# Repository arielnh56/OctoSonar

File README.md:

# OctoSonar library for Arduino
Version: 1.2.0<br>
Release date: 1/14/2018<br>
https://hackaday.io/project/19950-hc-sr04-i2c-octopus-octosonar
https://redhunterstore.etsy.com/listing/1151819630/octosonar-connect-8-x-hc-sr04-to-arduino

## Summary

This is a library for the Arduino IDE that allows the polling of multiple ultrasonic distance sensors using the I2C 
bus and a single hardware interrupt pin. It assumes a PCF8574(A) or PCF8575 type port expander to trigger the sensors, and 
tri-state buffers to multiplex the echo signals. It is specifically developed and maintained to support the author's 
OctoSonar boards version 2.0+ and OctoSonarX2. For earlier boards see the SonarI2C library.

It has been developed for use with the HC-SR04 sensor - and has been tested with units from multiple manufacturers.

## Supported Platforms

This library is designed to work with the Arduino IDE versions 1.6.x or later; it is not tested it with earlier versions. It should work with any Arduino compatible board with an available hardware interrupt pin. Note that other interrupt 
activity may interfere with the accuracy and reliability of this code.

## Getting Started

### Hardware

This code supports the OctoSonar v2.0 and later and OctoSonarX2. Schematics and board designs are included in this repo.

Boards and sensors can be purchased at [on Etsy.](https://redhunterstore.etsy.com)

The board should be connected to your controller as follows:

* GND -> GND
* VCC -> VCC (5V on the UNO)
* SDA -> SDA (A4 in the UNO)
* SCL -> SCL (A5 on the UNO)
* INT -> a hardware interrupt pin (2 or 3 on the UNO)
* 5V -> a 5V supply (VCC on the UNO)

Note that the 5V supply drives the sensors and the VCC drives the electronics. This allows the unit to be supported
on 3.3V controllers (some Arduino formats and Raspberry Pi, Teensy etc). You can save a wire on a 5V controller
by connecting the 5V and VCC pins together via the V1 solder jumper.

As manufactured the board has an I2C address of 0x38. This can be altered via solder jumpers on the back.

The I2C bus **requires** pullup resistors on the SDA and SCL lines to VCC. While Arduinos will enable the
internal pullups, these are too large at 20k - 50k for reliable operation of I2C. The generally recommended 
value to use is 4.7k. Positions are provided on the board at R1 and R2 to add these pullup resistors. On my 
projects I usually have several devices on the bus and place the pullups near the controller. For more information on
use of the I2C bus there is an [excellent Sparkfun tutorial.](https://learn.sparkfun.com/tutorials/i2c)

### Software

If you are using version 1.6.2 or later of the [Arduino software (IDE)](http://www.arduino.cc/en/Main/Software), you 
can use the Library Manager to install this library:

1. In the Arduino IDE, open the "Sketch" menu, select "Include Library", then "Manage Libraries...".
2. Search for "OctoSonar".
3. Click the OctoSonar entry in the list.
4. Click "Install".

If this does not work, you can manually install the library:

1. Download the [latest release archive from GitHub](https://github.com/arielnh56/OctoSonar/releases) and decompress it.
2. Rename the folder "OctoSonar-master" to "OctoSonar".
3. Move the "OctoSonar" folder into the "libraries" directory inside your Arduino sketchbook directory.  You can view your sketchbook location by opening the "File" menu and selecting "Preferences" in the Arduino IDE.  If there is not already a "libraries" folder in that location, you should make the folder yourself.
4. After installing the library, restart the Arduino IDE.

(note - the above instructions adapted from a Pololu readme)

## Examples

Examples are included to show basic functionality and use:

* OctoSonarTest - exercises the OctoSonar board and sends serial output at 115200 baud
* OctoSonarTestLCD - exercises the OctoSonar board and display output to LCD
* OctoSonarX2Test - exercises the OctoSonarX2 board and sends serial output at 115200 baud
* OctoSonarX2Test12LCD - exercises the OctoSonarX2 board and displays output on a two LCDs. Assumes 12 sensors mounted on my trimount brackets, with the diagonal sensor output displayed on the secondary LCD

The "bench" examples drive the test jigs used during quality control. Do no use these examples, they will not work for you.

## Library reference

* Constructor. Call once outside loop() and setup(). This sets the I2C address of the pin expander (0x38 - 0x3F for OctoSonar, 0x20 - 0x27 for OctoSonarX2).
e.g.  OctoSonar() myOcto;

 ```c
    OctoSonar(); // defaults constructor 0x38, 2
    OctoSonar(uint8_t address, uint8_t interrupt); // constructor
    OctoSonarX2(); // defaults constructor 0x20, 2
    OctoSonarX2(uint8_t address, uint8_t interrupt); // constructor
 
```

* call one of the begin() functions from setup(). The second one of these lets you set the active ports up front.
e.g. myOcto.begin();

 ```c
    void begin();
    void begin(uint16_t active);
```

*  Disabling sensors that you are not interested in right now allows the other sensors to poll more often. This is a bitmask mapping to the 16 sensors on the unit. A '1' is 'active'. 
e.g. myOcto.active = 0x0003;   // S0 and S1 only

 ```c
    uint16_t active;                    // mask of active sensors 
```

* by default we skip one out of range/failed echo, keeping the last value. It may be useful to raise this count in sub-optimal echo environments. This is a global setting.
e.g. OctoSonar::maxOOR = 2;

 ```c
    static uint8_t maxOOR;                                   // how many OOR to skip. Raise this in noisy environments
```

* by default the output is in mm. You can change this by setting this to OCTOSONAR_CM for cm, or OCTOSONAR_IN for inches. It is the value needed to convert from microseconds to the desired unit. This is a global setting.
e.g. OctoSonar::units = OCTOSONAR_IN;

 ```c
    static double units;                        // defaults to OCTOSONAR_MM 
```

* Call this every loop(). If it is time, it will poll the next enabled sensor. 
e.g. OctoSonar::doSonar();

 ```c
    static void doSonar();
```

* Return values. By default, when the sensor does not get a good echo a zero value is returned. Using the second
  form of read() allows you to set your own preference for what is returned. The returned value defaults to mm.
e.g. int16_t distance = myOcto.read(1);  // read distance from S1
 ```c
    int16_t read(uint8_t sonar);                     
    int16_t read(uint8_t sonar, int16_t outOfRange);
```

## Using multiple boards
The code is written to support multiple OctoSonar units on the same or different interrupt pins. It will cycle
through all the active sensors on one board, then move on to the next board, in a loop. It will not poll 
multiple boards in
parallel. At the time of writing (6/30/2017) I haven't actually tested this multi-board capability. It uses 
similar logic to that used in the earlier SonarI2C library, except that it is the boards that are in a 
looped-linked-list not the sensors.
 
## Relationship to SonarI2C

This is a rework of the SonarI2C concept, and borrows a lot from it. It is structurally different so I'm
 starting a new repo.

The main differences are:
* the use of tri-state buffers to mux the echo signals
* the trigger pulse is held down for the duration of each sensor. The falling edge triggers the HC-SR04, and the low value is used to enable the 
matching tri-state buffer to forward the echo signal
* the unit of thing is now the board, not the sensor. 
* No daisy-chaining. That was silly.

## Version history
* 1.2.0 (1/14/2018): Updated eagle files. Updated examples. No changes to library code.
* 1.1.0 (7/26/2017): OctoSonarX2 support working - moved to derived classes
* 1.0.1 (7/1/2017): Included correct OctoSonarTest example
* 1.0.0 (06/30/2017): Initial release

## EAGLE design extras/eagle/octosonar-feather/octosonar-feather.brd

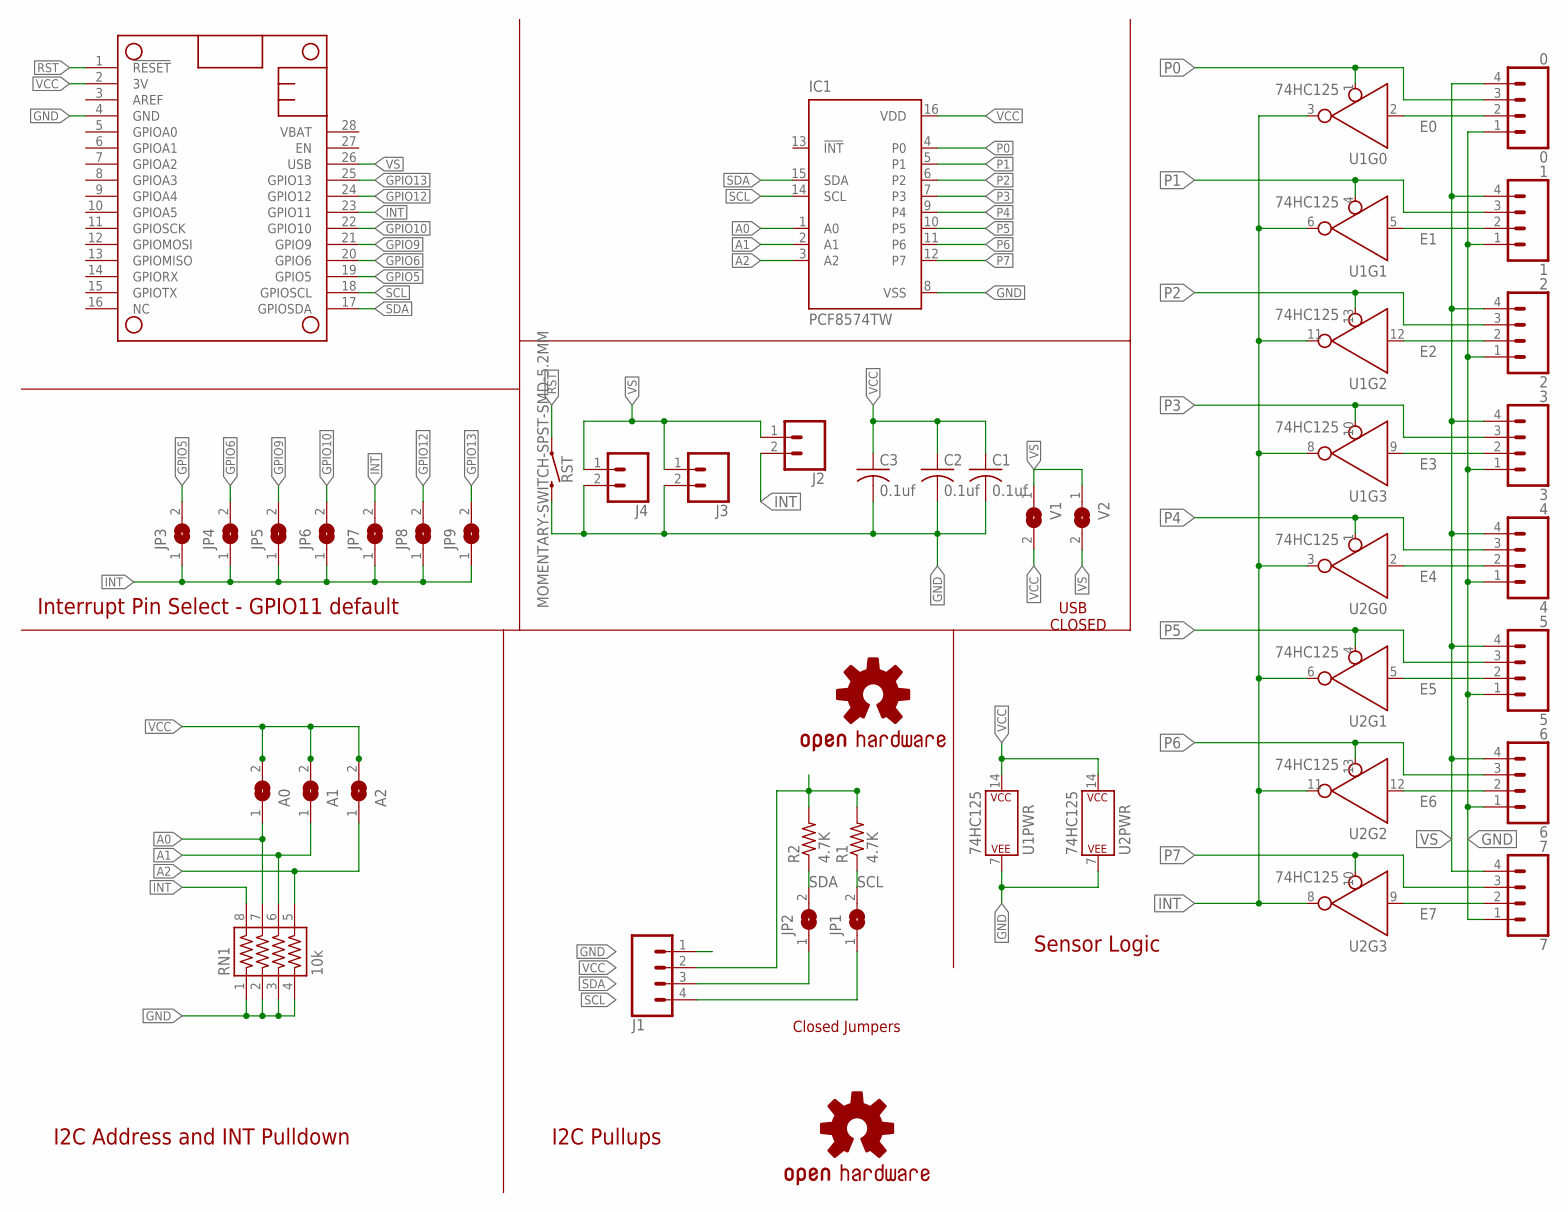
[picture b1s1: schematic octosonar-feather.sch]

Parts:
0: 0; 1X04_NO_SILK
1: 1; 1X04_NO_SILK
2: 2; 1X04_NO_SILK
3: 3; 1X04_NO_SILK
4: 4; 1X04_NO_SILK
5: 5; 1X04_NO_SILK
6: 6; 1X04_NO_SILK
7: 7; 1X04_NO_SILK
A0, A1, A2: SJSJ-NOCREAM; SJ-NOCREAM
C1, C2, C3: 0.1uf; C0603
IC1: PCF8574TW; SO16W
J1: CONN_041X04_NO_SILK; 1X04_NO_SILK
J2, J3, J4: CONN_021X02_NO_SILK; 1X02_NO_SILK
JP1, JP2, JP3, JP4, JP5, JP6, JP7, JP8, JP9: SJSJ-NOCREAM; SJ-NOCREAM
LOGO1: OSHW-LOGOL-COPPER; OSHW-LOGO-L_COPPER
LOGO2: OSHW-LOGOL; OSHW-LOGO-L
MS1: FEATHERWINGFEATHERWING_LONG; FEATHERWING_LONG
R1, R2: 4.7K; R0603
RN1: 10k; 743-8
RST: MOMENTARY-SWITCH-SPST-SMD-5.2MM; TACTILE_SWITCH_SMD_5.2MM
U1, U2: 74HC125; SO14
V1, V2: SJSJ-NOCREAM; SJ-NOCREAM

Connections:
A0: A0.1, IC1.1 (A0), RN1.7
A1: A1.1, IC1.2 (A1), RN1.6
A2: A2.1, IC1.3 (A2), RN1.5
E0: 0.2, U1.2 (A)
E1: 1.2, U1.5 (A)
E2: 2.2, U1.12 (A)
E3: 3.2, U1.9 (A)
E4: 4.2, U2.2 (A)
E5: 5.2, U2.5 (A)
E6: 6.2, U2.12 (A)
E7: 7.2, U2.9 (A)
GND: 0.1, 1.1, 2.1, 3.1, 4.1, 5.1, 6.1, 7.1, C1.2, C2.2, C3.2, IC1.8 (VSS), J1.1, J3.2, J4.2, MS1.4 (GND), RN1.1, RN1.2, RN1.3, RN1.4, RST.3 (2), U1.7 (P$V-), U2.7 (P$V-)
GPIO5: JP3.2, MS1.19 (GPIO5)
GPIO6: JP4.2, MS1.20 (GPIO6)
GPIO9: JP5.2, MS1.21 (GPIO9)
GPIO10: JP6.2, MS1.22 (GPIO10)
GPIO12: JP8.2, MS1.24 (GPIO12)
GPIO13: JP9.2, MS1.25 (GPIO13)
INT: J2.2, JP3.1, JP4.1, JP5.1, JP6.1, JP7.1, JP7.2, JP8.1, JP9.1, MS1.23 (GPIO11), RN1.8, U1.3 (Y), U1.6 (Y), U1.8 (Y), U1.11 (Y), U2.3 (Y), U2.6 (Y), U2.8 (Y), U2.11 (Y)
P0: 0.3, IC1.4 (P0), U1.1 (!EN)
P1: 1.3, IC1.5 (P1), U1.4 (!EN)
P2: 2.3, IC1.6 (P2), U1.13 (!EN)
P3: 3.3, IC1.7 (P3), U1.10 (!EN)
P4: 4.3, IC1.9 (P4), U2.1 (!EN)
P5: 5.3, IC1.10 (P5), U2.4 (!EN)
P6: 6.3, IC1.11 (P6), U2.13 (!EN)
P7: 7.3, IC1.12 (P7), U2.10 (!EN)
RST: MS1.1 (!RESET), RST.1
SCL: IC1.14 (SCL), J1.4, JP1.1, JP1.2, MS1.18 (GPIOSCL), R1.1
SDA: IC1.15 (SDA), J1.3, JP2.1, JP2.2, MS1.17 (GPIOSDA), R2.1
VCC: A0.2, A1.2, A2.2, C1.1, C2.1, C3.1, IC1.16 (VDD), J1.2, MS1.2 (3V), R1.2, R2.2, U1.14 (P$V+), U2.14 (P$V+), V1.2
VS: 0.4, 1.4, 2.4, 3.4, 4.4, 5.4, 6.4, 7.4, J2.1, J3.1, J4.1, MS1.26 (USB), V1.1, V2.1, V2.2

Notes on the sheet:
Sensor Logic
I2C Pullups
I2C Address and INT Pulldown
Interrupt Pin Select - GPIO11 default
USB CLOSED
Closed Jumpers

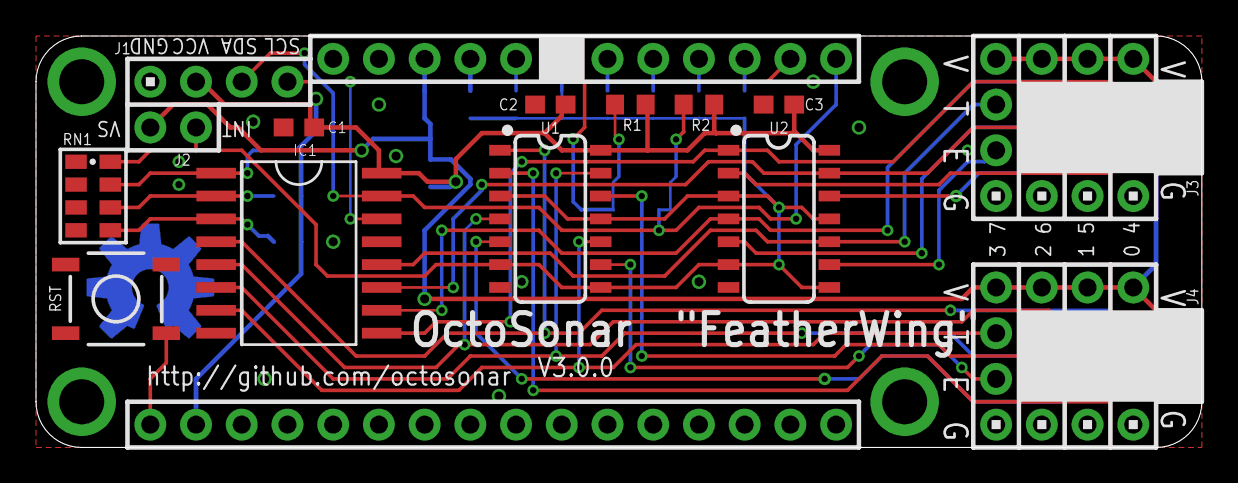
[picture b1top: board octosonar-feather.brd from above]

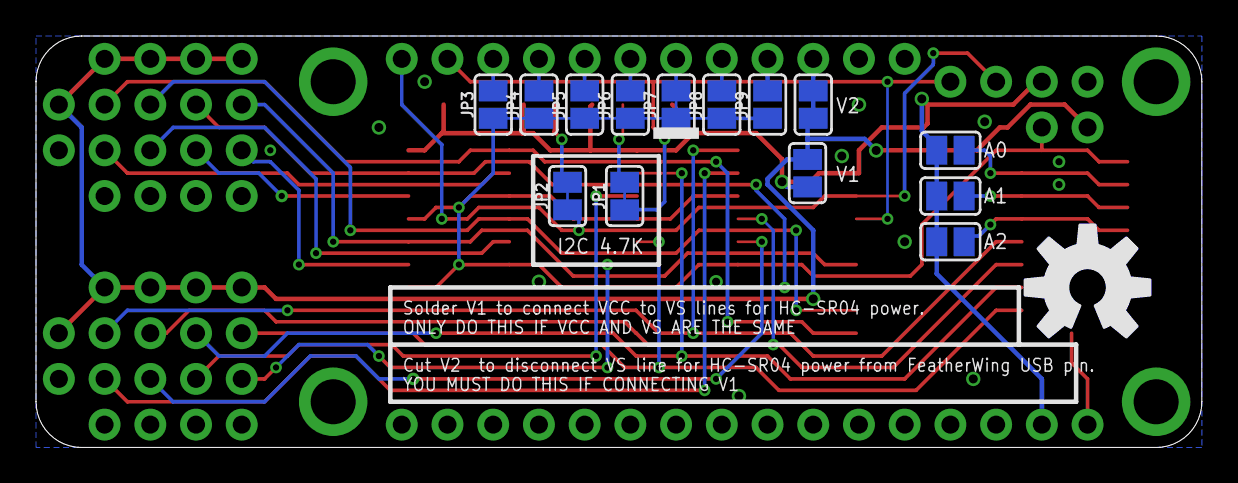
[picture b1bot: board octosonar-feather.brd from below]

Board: 2 copper layers, 64.8 x 22.9 mm, 39 parts (16 on the bottom side), 32 nets.

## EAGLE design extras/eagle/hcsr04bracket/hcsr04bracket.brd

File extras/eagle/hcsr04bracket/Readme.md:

This is the 1.0.0 initial batch. The diagonal sensor is 0.1" too far back, so
the pins on that sensor need re-bending.

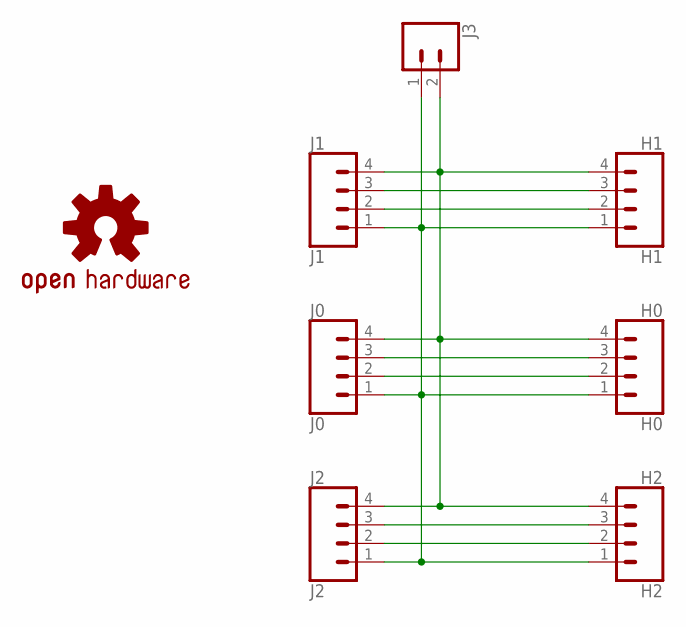
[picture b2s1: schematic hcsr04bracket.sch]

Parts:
H0: H0; 1X04
H1: H1; 1X04
H2: H2; 1X04
J0: J0; 1X04
J1: J1; 1X04
J2: J2; 1X04
J3: CONN_02; 1X02
LOGO1: OSHW-LOGOS; OSHW-LOGO-S

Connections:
E1: H1.3, J1.3
E2: H0.3, J0.3
E3: H2.3, J2.3
GND: H0.4, H1.4, H2.4, J0.4, J1.4, J2.4, J3.2
T1: H1.2, J1.2
T2: H0.2, J0.2
T3: H2.2, J2.2
VCC: H0.1, H1.1, H2.1, J0.1, J1.1, J2.1, J3.1

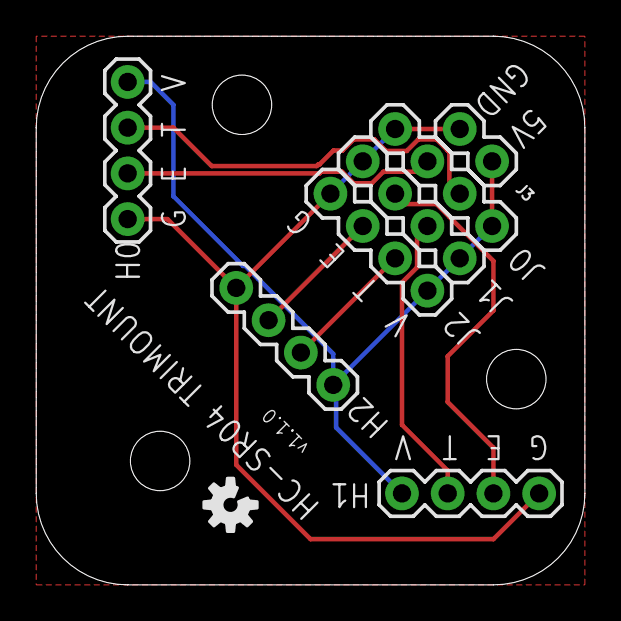
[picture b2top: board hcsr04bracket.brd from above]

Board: 2 copper layers, 30.5 x 30.5 mm, 11 parts (1 on the bottom side), 8 nets.

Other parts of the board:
U$1, U$2, U$3: STAND-OFF

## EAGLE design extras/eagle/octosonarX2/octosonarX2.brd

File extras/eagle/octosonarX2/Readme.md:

This is 1.0.0 batch.

It differs from the 0.0.1 prototype with changes in bypass caps and a re-routing
of the power around the board with a wider track. This now runs closer than
ideal to the bottom left mounting hole so I ship a plastic screw with it.
That should be fixed in the next batch.

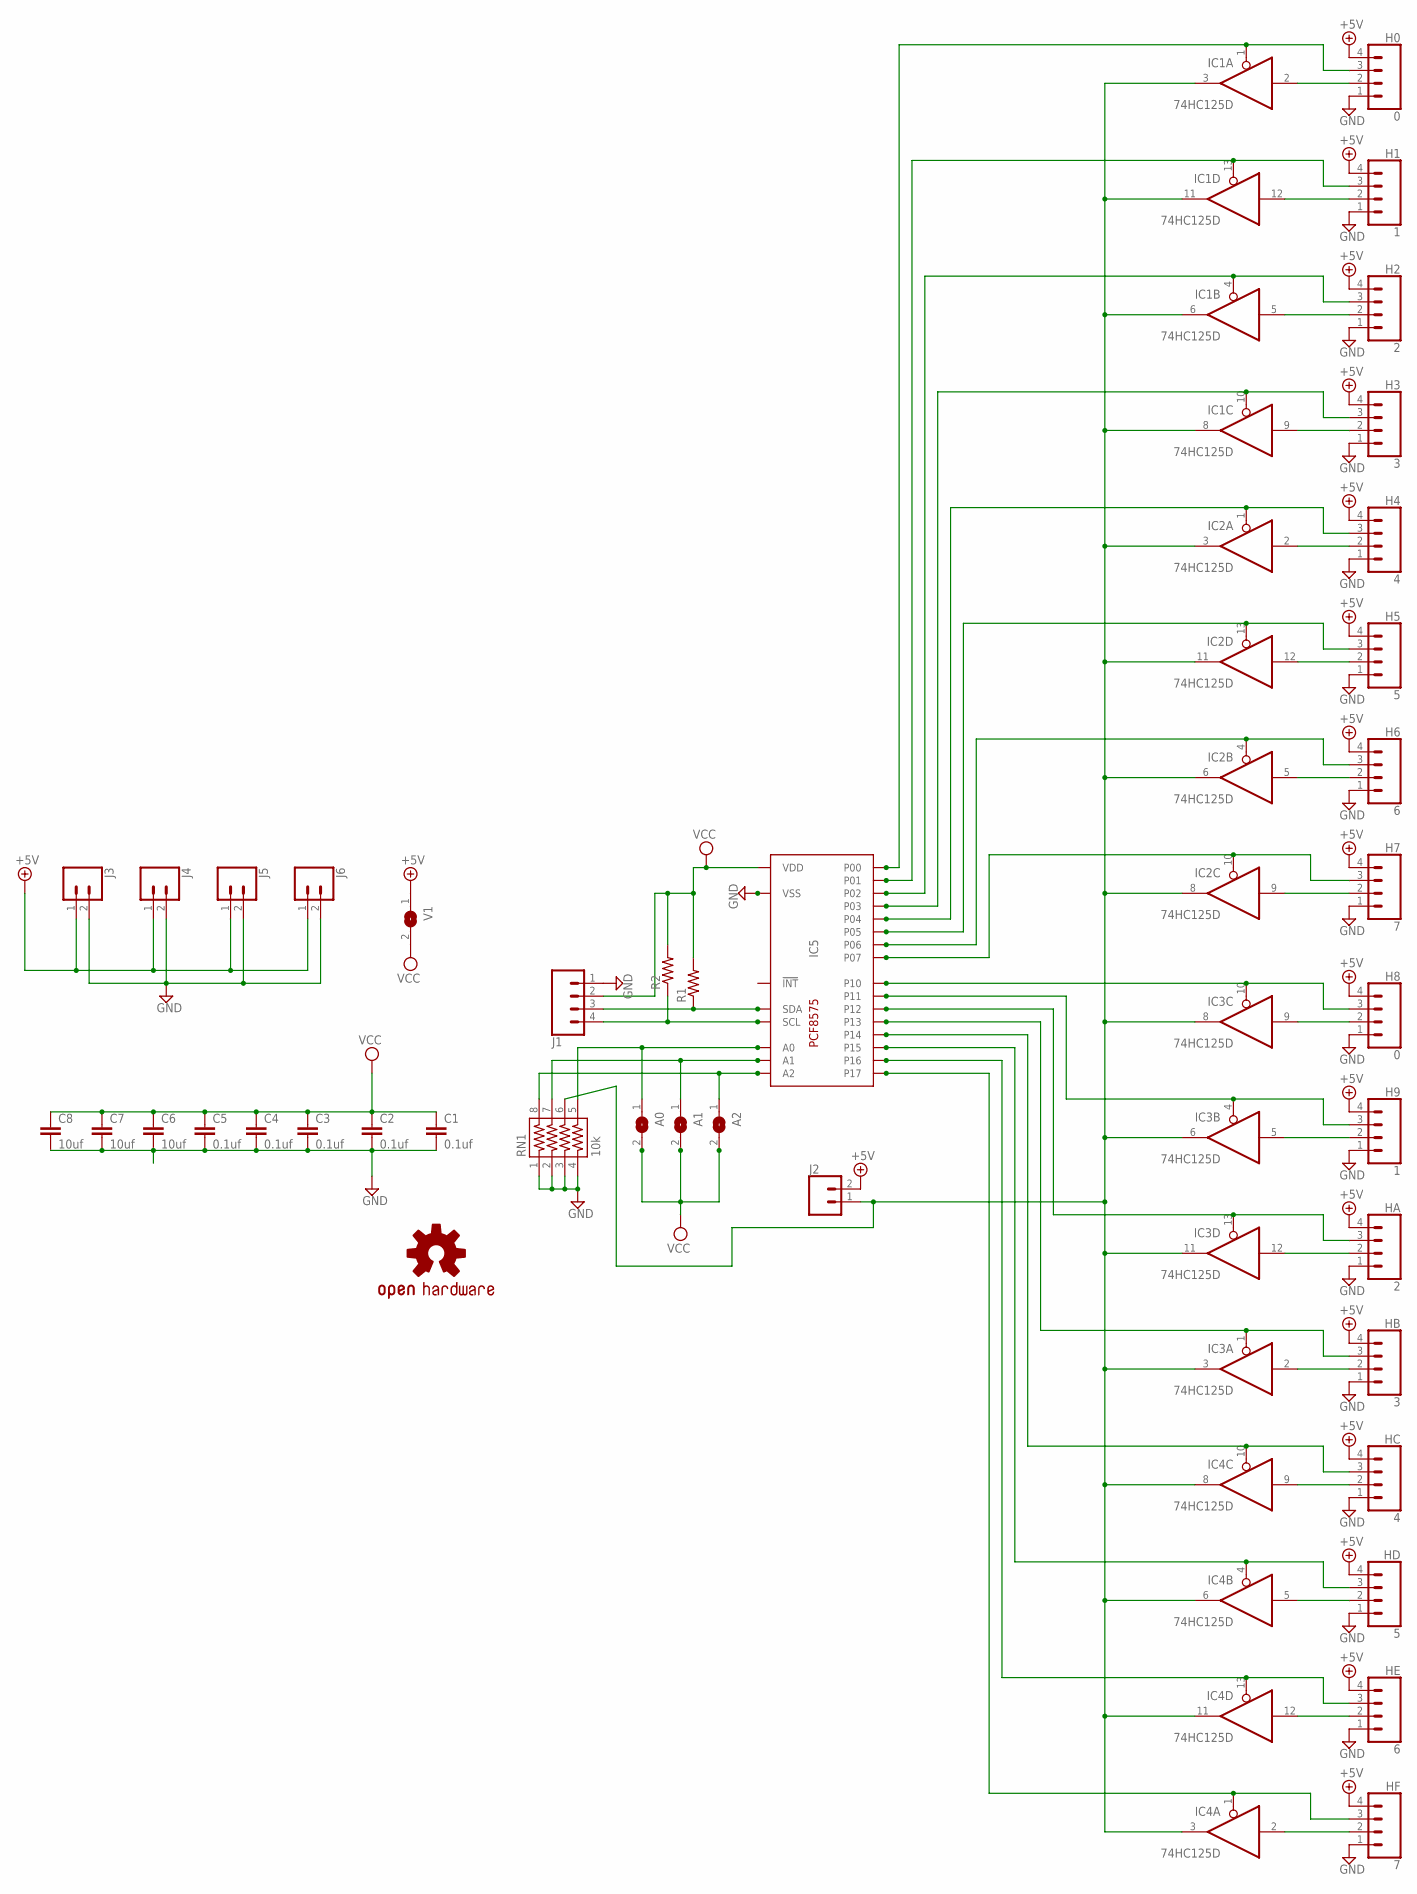
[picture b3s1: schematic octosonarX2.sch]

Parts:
A0, A1, A2: SJ
C1, C2, C3, C4, C5: 0.1uf; C0603
C6: 10uf; C0603
C7, C8: 10uf; C0805
H0, H8: 0; 1X04
H1, H9: 1; 1X04
H2: 2; 1X04
H3: 3; 1X04
H4: 4; 1X04
H5: 5; 1X04
H6: 6; 1X04
H7: 7; 1X04
HA: 2; 1X04
HB: 3; 1X04
HC: 4; 1X04
HD: 5; 1X04
HE: 6; 1X04
HF: 7; 1X04
IC1, IC2, IC3, IC4: 74HC125D; SO14
IC5: PCF8575C; SOP24
J1: CONN_04POLAR_LOCK; MOLEX-1X4_LOCK
J2: CONN_02POLAR_LOCK; MOLEX-1X2_LOCK
J3, J4, J5, J6: CONN_02; 1X02
LOGO1: OSHW-LOGOL; OSHW-LOGO-L
R1, R2: R-US_0204/2V; 0204V
RN1: 10k; 743-8
V1: SJ

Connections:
+5V: H0.4, H1.4, H2.4, H3.4, H4.4, H5.4, H6.4, H7.4, H8.4, H9.4, HA.4, HB.4, HC.4, HD.4, HE.4, HF.4, J2.2, J3.1, J4.1, J5.1, J6.1, V1.1
GND: C1.2, C2.2, C3.2, C4.2, C5.2, C6.2, C7.2, C8.2, H0.1, H1.1, H2.1, H3.1, H4.1, H5.1, H6.1, H7.1, H8.1, H9.1, HA.1, HB.1, HC.1, HD.1, HE.1, HF.1, IC1.7 (GND), IC2.7 (GND), IC3.7 (GND), IC4.7 (GND), IC5.P$12 (VSS), J1.1, J3.2, J4.2, J5.2, J6.2, RN1.1, RN1.2, RN1.3, RN1.4
INT: IC1.3 (O), IC1.6 (O), IC1.8 (O), IC1.11 (O), IC2.3 (O), IC2.6 (O), IC2.8 (O), IC2.11 (O), IC3.3 (O), IC3.6 (O), IC3.8 (O), IC3.11 (O), IC4.3 (O), IC4.6 (O), IC4.8 (O), IC4.11 (O), J2.1, RN1.6
unnamed: H8.3, IC3.10 (OE), IC5.P$13 (P10)
unnamed: H9.3, IC3.4 (OE), IC5.P$14 (P11)
unnamed: HA.3, IC3.13 (OE), IC5.P$15 (P12)
unnamed: HB.3, IC3.1 (OE), IC5.P$16 (P13)
unnamed: HC.3, IC4.10 (OE), IC5.P$17 (P14)
unnamed: HD.3, IC4.4 (OE), IC5.P$18 (P15)
unnamed: HE.3, IC4.13 (OE), IC5.P$19 (P16)
unnamed: HF.3, IC4.1 (OE), IC5.P$20 (P17)
unnamed: H8.2, IC3.9 (I)
unnamed: H9.2, IC3.5 (I)
unnamed: HA.2, IC3.12 (I)
unnamed: HB.2, IC3.2 (I)
unnamed: HD.2, IC4.5 (I)
unnamed: HE.2, IC4.12 (I)
unnamed: HF.2, IC4.2 (I)
unnamed: HC.2, IC4.9 (I)
unnamed: A2.1, IC5.P$3 (A2), RN1.8
unnamed: A1.1, IC5.P$2 (A1), RN1.7
unnamed: A0.1, IC5.P$21 (A0), RN1.5
unnamed: H0.3, IC1.1 (OE), IC5.P$4 (P00)
unnamed: H1.3, IC1.13 (OE), IC5.P$5 (P01)
unnamed: H2.3, IC1.4 (OE), IC5.P$6 (P02)
unnamed: H3.3, IC1.10 (OE), IC5.P$7 (P03)
unnamed: H4.3, IC2.1 (OE), IC5.P$8 (P04)
unnamed: H5.3, IC2.13 (OE), IC5.P$9 (P05)
unnamed: H6.3, IC2.4 (OE), IC5.P$10 (P06)
unnamed: H7.3, IC2.10 (OE), IC5.P$11 (P07)
unnamed: H0.2, IC1.2 (I)
unnamed: H1.2, IC1.12 (I)
unnamed: H2.2, IC1.5 (I)
unnamed: H3.2, IC1.9 (I)
unnamed: H5.2, IC2.12 (I)
unnamed: H6.2, IC2.5 (I)
unnamed: H7.2, IC2.9 (I)
unnamed: H4.2, IC2.2 (I)
SCL: IC5.P$22 (SCL), J1.4, R2.1
SDA: IC5.P$23 (SDA), J1.3, R1.1
VCC: A0.2, A1.2, A2.2, C1.1, C2.1, C3.1, C4.1, C5.1, C6.1, C7.1, C8.1, IC1.14 (VCC), IC2.14 (VCC), IC3.14 (VCC), IC4.14 (VCC), IC5.P$24 (VDD), J1.2, R1.2, R2.2, V1.2

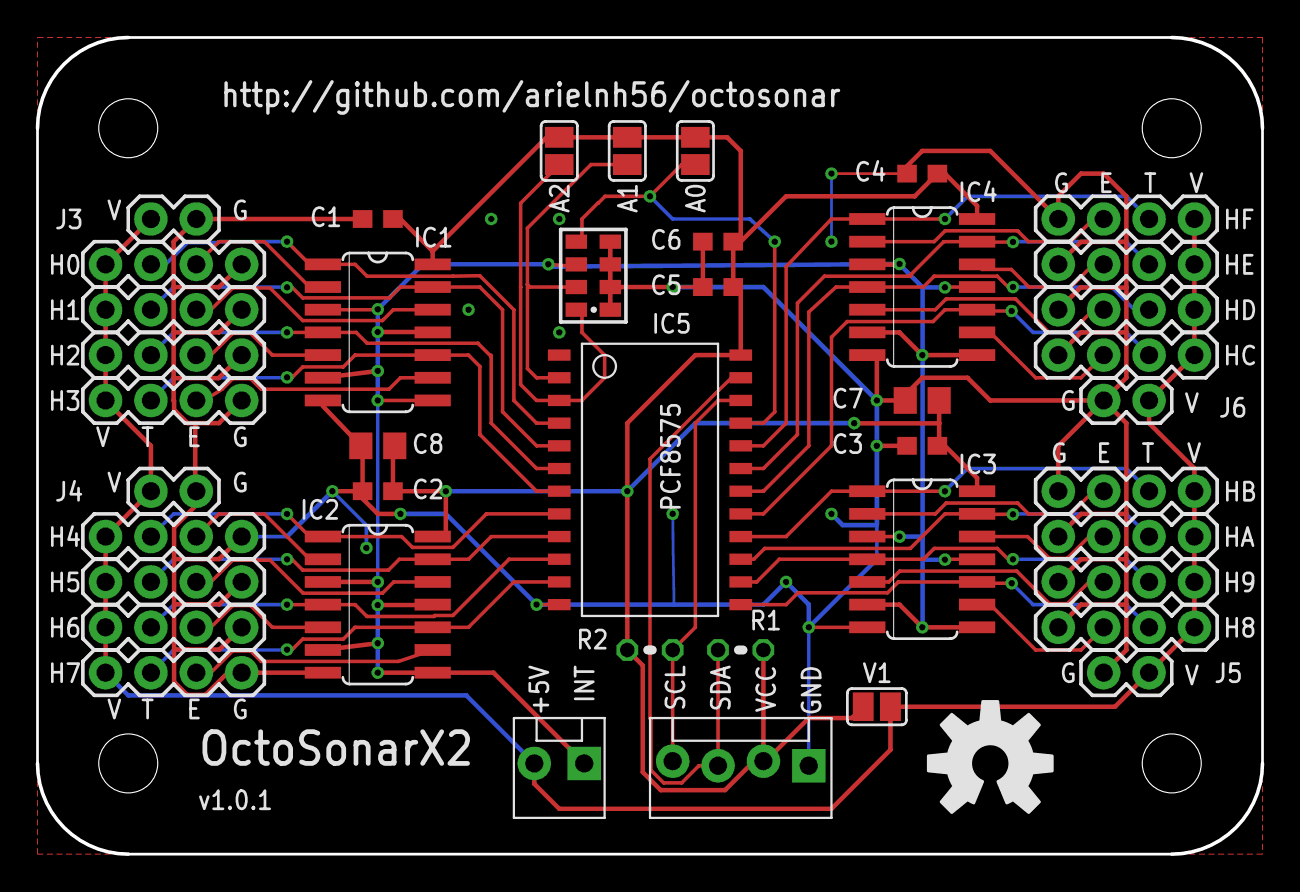
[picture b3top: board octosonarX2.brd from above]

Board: 2 copper layers, 68.6 x 45.7 mm, 47 parts (0 on the bottom side), 41 nets.

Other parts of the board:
U$2, U$3, U$4, U$5: STAND-OFF

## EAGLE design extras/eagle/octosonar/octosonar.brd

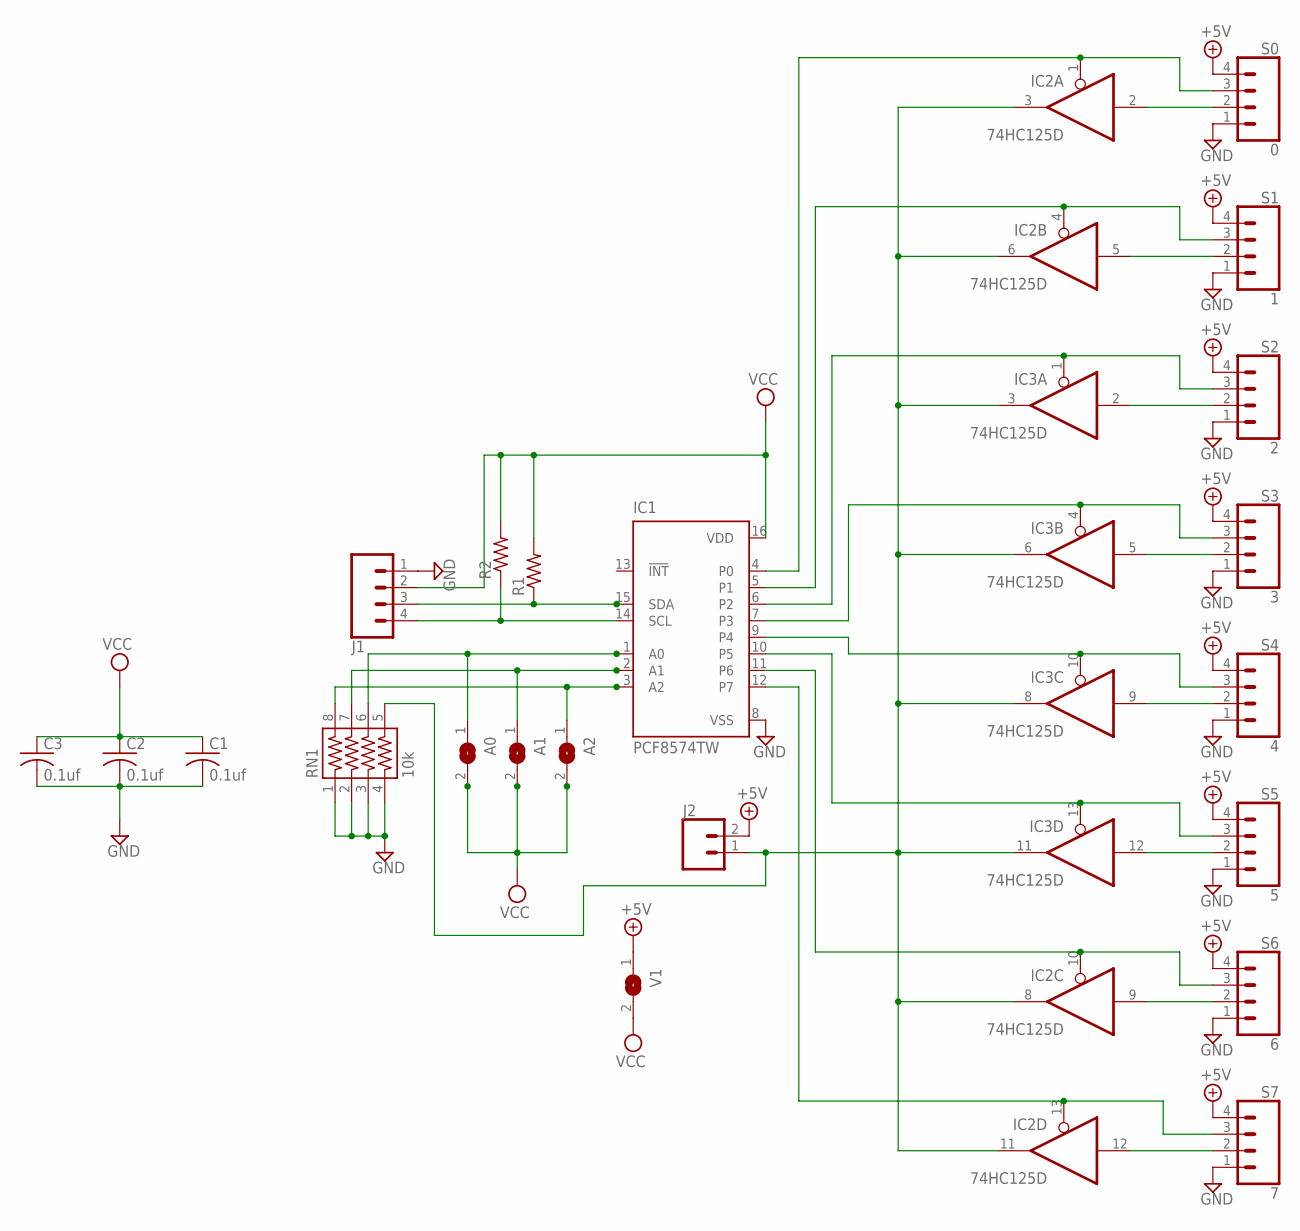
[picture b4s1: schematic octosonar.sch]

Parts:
A0, A1, A2: SJ
C1, C2, C3: 0.1uf; C0805
IC1: PCF8574TW; SO16W
IC2, IC3: 74HC125D; SO14
J1: CONN_04POLAR_LOCK; MOLEX-1X4_LOCK
J2: CONN_02POLAR_LOCK; MOLEX-1X2_LOCK
R1, R2: R-US_0204/2V; 0204V
RN1: 10k; 743-8
S0: 0; MOLEX-1X4_LOCK
S1: 1; MOLEX-1X4_LOCK
S2: 2; MOLEX-1X4_LOCK
S3: 3; MOLEX-1X4_LOCK
S4: 4; MOLEX-1X4_LOCK
S5: 5; MOLEX-1X4_LOCK
S6: 6; MOLEX-1X4_LOCK
S7: 7; MOLEX-1X4_LOCK
V1: SJ

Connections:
+5V: J2.2, S0.4, S1.4, S2.4, S3.4, S4.4, S5.4, S6.4, S7.4, V1.1
GND: C1.2, C2.2, C3.2, IC1.8 (VSS), IC2.7 (GND), IC3.7 (GND), J1.1, RN1.1, RN1.2, RN1.3, RN1.4, S0.1, S1.1, S2.1, S3.1, S4.1, S5.1, S6.1, S7.1
unnamed: IC1.4 (P0), IC2.1 (OE), S0.3
unnamed: IC1.5 (P1), IC2.4 (OE), S1.3
unnamed: IC1.6 (P2), IC3.1 (OE), S2.3
unnamed: IC1.7 (P3), IC3.4 (OE), S3.3
unnamed: IC1.9 (P4), IC3.10 (OE), S4.3
unnamed: IC1.10 (P5), IC3.13 (OE), S5.3
unnamed: IC1.11 (P6), IC2.10 (OE), S6.3
unnamed: IC1.12 (P7), IC2.13 (OE), S7.3
unnamed: IC2.2 (I), S0.2
unnamed: IC2.5 (I), S1.2
unnamed: IC3.2 (I), S2.2
unnamed: IC3.5 (I), S3.2
unnamed: IC3.12 (I), S5.2
unnamed: IC2.9 (I), S6.2
unnamed: IC2.12 (I), S7.2
unnamed: IC3.9 (I), S4.2
unnamed: IC2.3 (O), IC2.6 (O), IC2.8 (O), IC2.11 (O), IC3.3 (O), IC3.6 (O), IC3.8 (O), IC3.11 (O), J2.1, RN1.5
unnamed: A2.1, IC1.3 (A2), RN1.8
unnamed: A1.1, IC1.2 (A1), RN1.7
unnamed: A0.1, IC1.1 (A0), RN1.6
unnamed: IC1.14 (SCL), J1.4, R2.1
unnamed: IC1.15 (SDA), J1.3, R1.1
VCC: A0.2, A1.2, A2.2, C1.1, C2.1, C3.1, IC1.16 (VDD), IC2.14 (VCC), IC3.14 (VCC), J1.2, R1.2, R2.2, V1.2

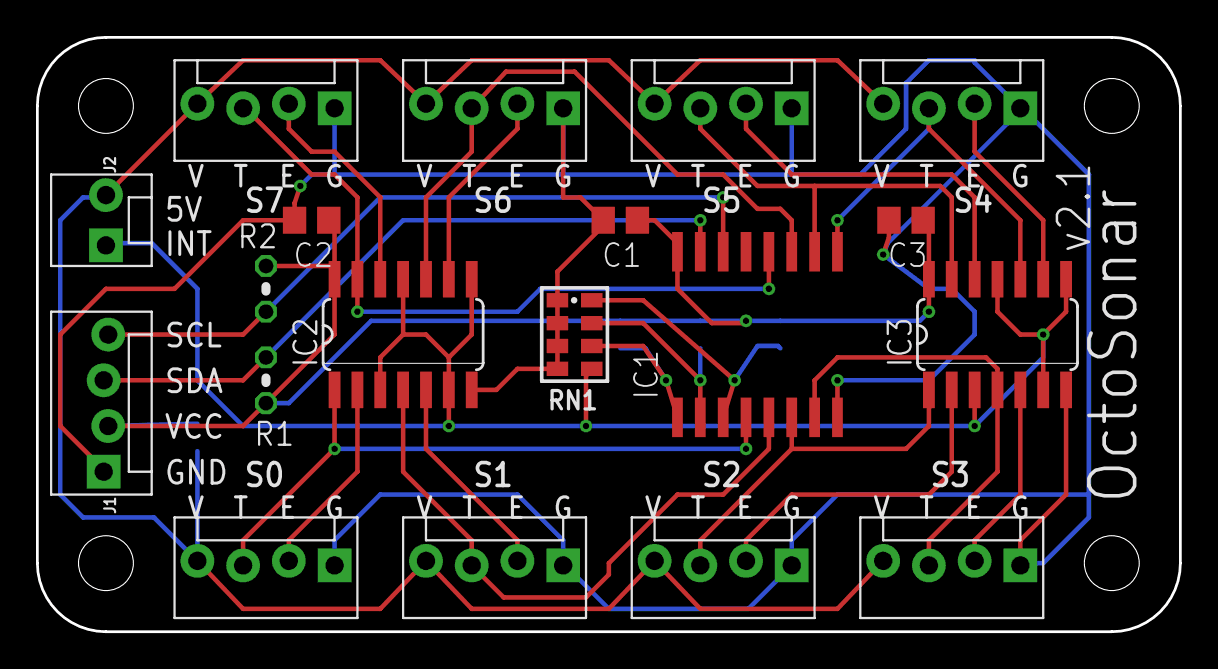
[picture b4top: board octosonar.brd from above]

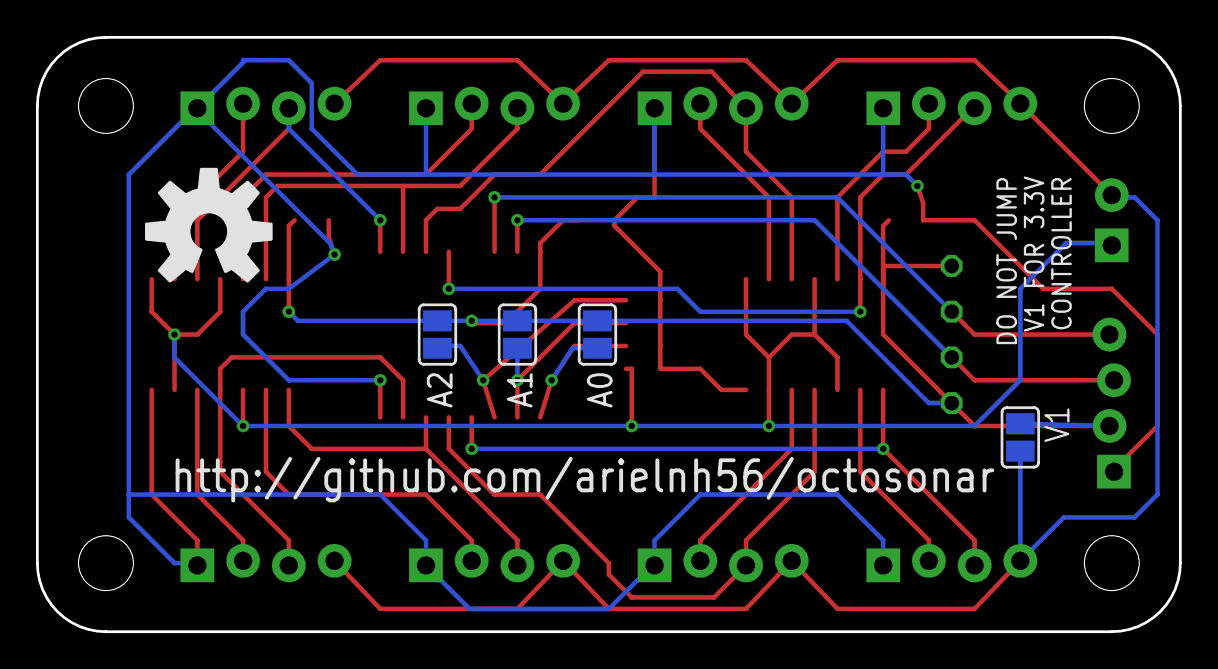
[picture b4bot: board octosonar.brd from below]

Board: 2 copper layers, 63.5 x 33.0 mm, 28 parts (5 on the bottom side), 25 nets.

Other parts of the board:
U$1, U$2, U$3, U$4: STAND-OFF-TIGHT
U$5: OSHW-LOGO-L

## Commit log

2017-06-03 Added read function with default override
    It can be useful to assume OOR is "big" rather than zero.
2017-06-03 remove vi dross
    darned swp files
2017-06-04 First pass at readme
    also license
    also added missing things in the .h file
2017-06-07 Added eagle files octosonar 2.0
    Octosonar 2.0 prototype OSHPark
2017-06-09 octosonar board 2.1 first pass
    input pins on grid
    add i2c pullups
    silkscreen rework
    full re-route
2017-06-09 add 2.1 pictures
2017-06-09 hires 2.1 images
    thank you OSHPark
2017-06-25 added octosonar_bench.ino
    This is example is what I use to drive the bench test for new boards.
    The jig is made of two V2.1 boards that had bad silkscreen and
    pogo-pins. The lower board has a PCF8574 at 0x20 so it can spy on the
    TRIG signals being sent to the test board. The echo pins are driven from
    arduino digital pins.
    I ran into horrible problems writing things to the test board and
2017-07-01 Release 1.0.0
    Code updated and tested on one board ready for initial release.
    Main changes are to clarify which variables are class and which are
    instance and to add looping through multiple boards. Multiple board
    testing will happen soon and will be logged on hackaday.
    https://hackaday.io/project/19950-hc-sr04-i2c-octopus-octosonar
2017-07-01 Minor readme tweaks for 1.0.0 release
2017-07-01 Included correct OctoSonarTest.ino
2017-07-27 Add working support for OctoSonarX2
    The ifdef settings in the previous version did not actually work in
    practice. The two board types are now derived classes from a base, and
    the code alters behavior when it has to write to the 16 bit PCF8575 on
    the X2. The only api difference is that the active value is now
    uint16_t not uint8_t. This should be backwards compatible.
2017-07-30 Add hcsr04bracket eagle files
    this is the original prototype, needs tweaking
2018-01-12 Updates to X2 test and trimount bracket
    Updates X2 test
    Updated trimount bracket - moved diagonal sensor back
2018-01-12 Revert "Updates to X2 test and trimount bracket"
    This reverts commit f0c77c11ce1398fcc169d7c2890869ee86536cf6.
2018-01-15 1.2.0 eagle files and examples updated
    Eagle files updated for OctoSonarX2 and Trimounts to reflect modifications between prototype and production.
    OctoSonarX2 - tweaked bypass caps. Rerouted 5V with wider traces.
    Examples - tidies up with serial only tests and separate LCD tests.
2019-08-11 Update octosonarX2.brd to 1.0.1
    Moved the 5V line away from the screw hole by moving it to bottom layer. This never caused any reported problem, but I was worried about it and was supplying a plastic screw with each unit just in ca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
2019-08-11 Update hcsr04bracket.brd to 1.1.0
    Moved diagonal mount out to correct position. Fixed floodfill.
2019-08-11 Misc eagle cleanup
    Design rule tweaks etc for gerber generation.
2019-11-10 Add prototype Octosonar FeatherWing
    Initial pass for Hackaday challenge
2019-11-10 forgot the brd file
2019-11-11 feather tweaks
    tenting, matching diameters on 0.1" headers etc. Updated images
2019-11-11 Changed caps to correct footprint
    They were 0804 should be 0603. I changed to 0603 0.1uF a long time ago.
2019-12-31 Octosonar v3.0.0 prod featherwing design
2022-01-17 Update octosonarx2_bench.ino
    checked in version was not the one I was actually using
2026-02-05 Update README.md
    Update retail links

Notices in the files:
parts and their libraries:
SparkFun-Connectors: Licensing: Creative Commons ShareAlike 4.0 International - https://creativecommons.org/licenses/by-sa/4.0
resistor-array: Copyright (C) 2008, Bob Starr
